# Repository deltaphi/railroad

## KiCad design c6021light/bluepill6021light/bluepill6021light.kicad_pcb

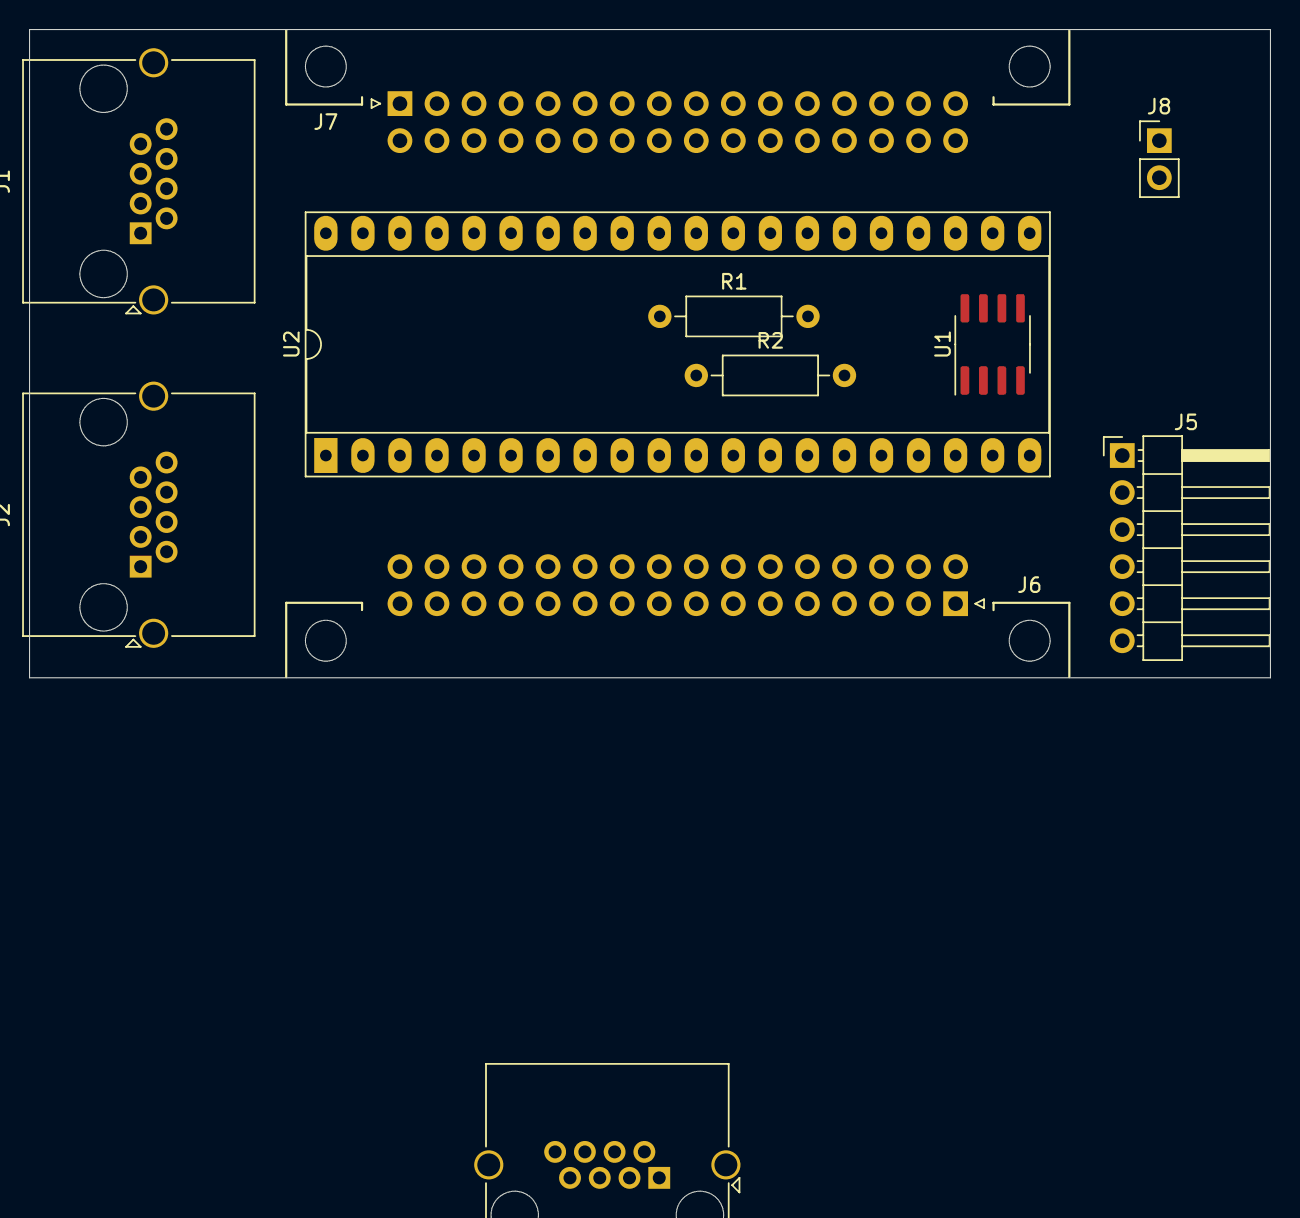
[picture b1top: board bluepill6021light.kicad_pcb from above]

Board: 2 copper layers, 85.1 x 44.4 mm, 11 parts (0 on the bottom side), 15 nets, no tracks yet.

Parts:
J1: CAN1; RJ45_Amphenol_RJHSE5380
J2: CAN2; RJ45_Amphenol_RJHSE5380
J3: I2CKeyboard2; RJ45_Amphenol_RJHSE5380
J5: Serial; PinHeader_1x06_P2.54mm_Horizontal
J6: I2CKeyboard; DIN41612_B2_2x16_Horizontal
J7: I2CControl; DIN41612_B2_2x16_Horizontal
J8: USB_PWR; PinHeader_1x02_P2.54mm_Vertical
R1, R2: 10k; R_Axial_DIN0207_L6.3mm_D2.5mm_P10.16mm_Horizontal
U1: TJA1051T-E; SOIC-8_3.9x4.9mm_P1.27mm
U2: STM32-BARE; DIP-40_W15.24mm_Socket_LongPads

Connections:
/5V: J8.1, U2.18
/CANH: J1.1, J2.1, U1.7
/CANL: J1.2, J2.2, U1.6
/CANRX: U1.4, U2.16
/CANTX: U1.1, U2.17
/Gleisbox_Supply: J1.3, J1.4, J2.3, J2.4
/RX0: J5.4, U2.7
/SCL: R1.2, U2.14
/SDA: R2.2, U2.15
/TX0: J5.5, U2.6
/Track_Brown: J1.7, J2.7
/Track_Red: J1.8, J2.8
GND: J1.5, J1.6, J1.SH, J2.5, J2.6, J2.SH, J3.SH, J5.1, U1.2, U2.19, U2.39, U2.40
unnamed: J5.3, J8.2
VCC: R1.1, R2.1, U1.3, U2.20, U2.38

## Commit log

2020-05-24 Initial Checkin of KiCAD files for BluePill 6021
2020-05-24 Added basic infrastructure
2020-05-24 Added KiCAD .gitignore
2020-05-25 Added initial PCB
2020-06-03 Extended Debugging Output on CAN Transmission
